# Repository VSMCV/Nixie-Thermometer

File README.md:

# Nixie-Thermometer
Hardware design and software files for a Nixie display thermometer

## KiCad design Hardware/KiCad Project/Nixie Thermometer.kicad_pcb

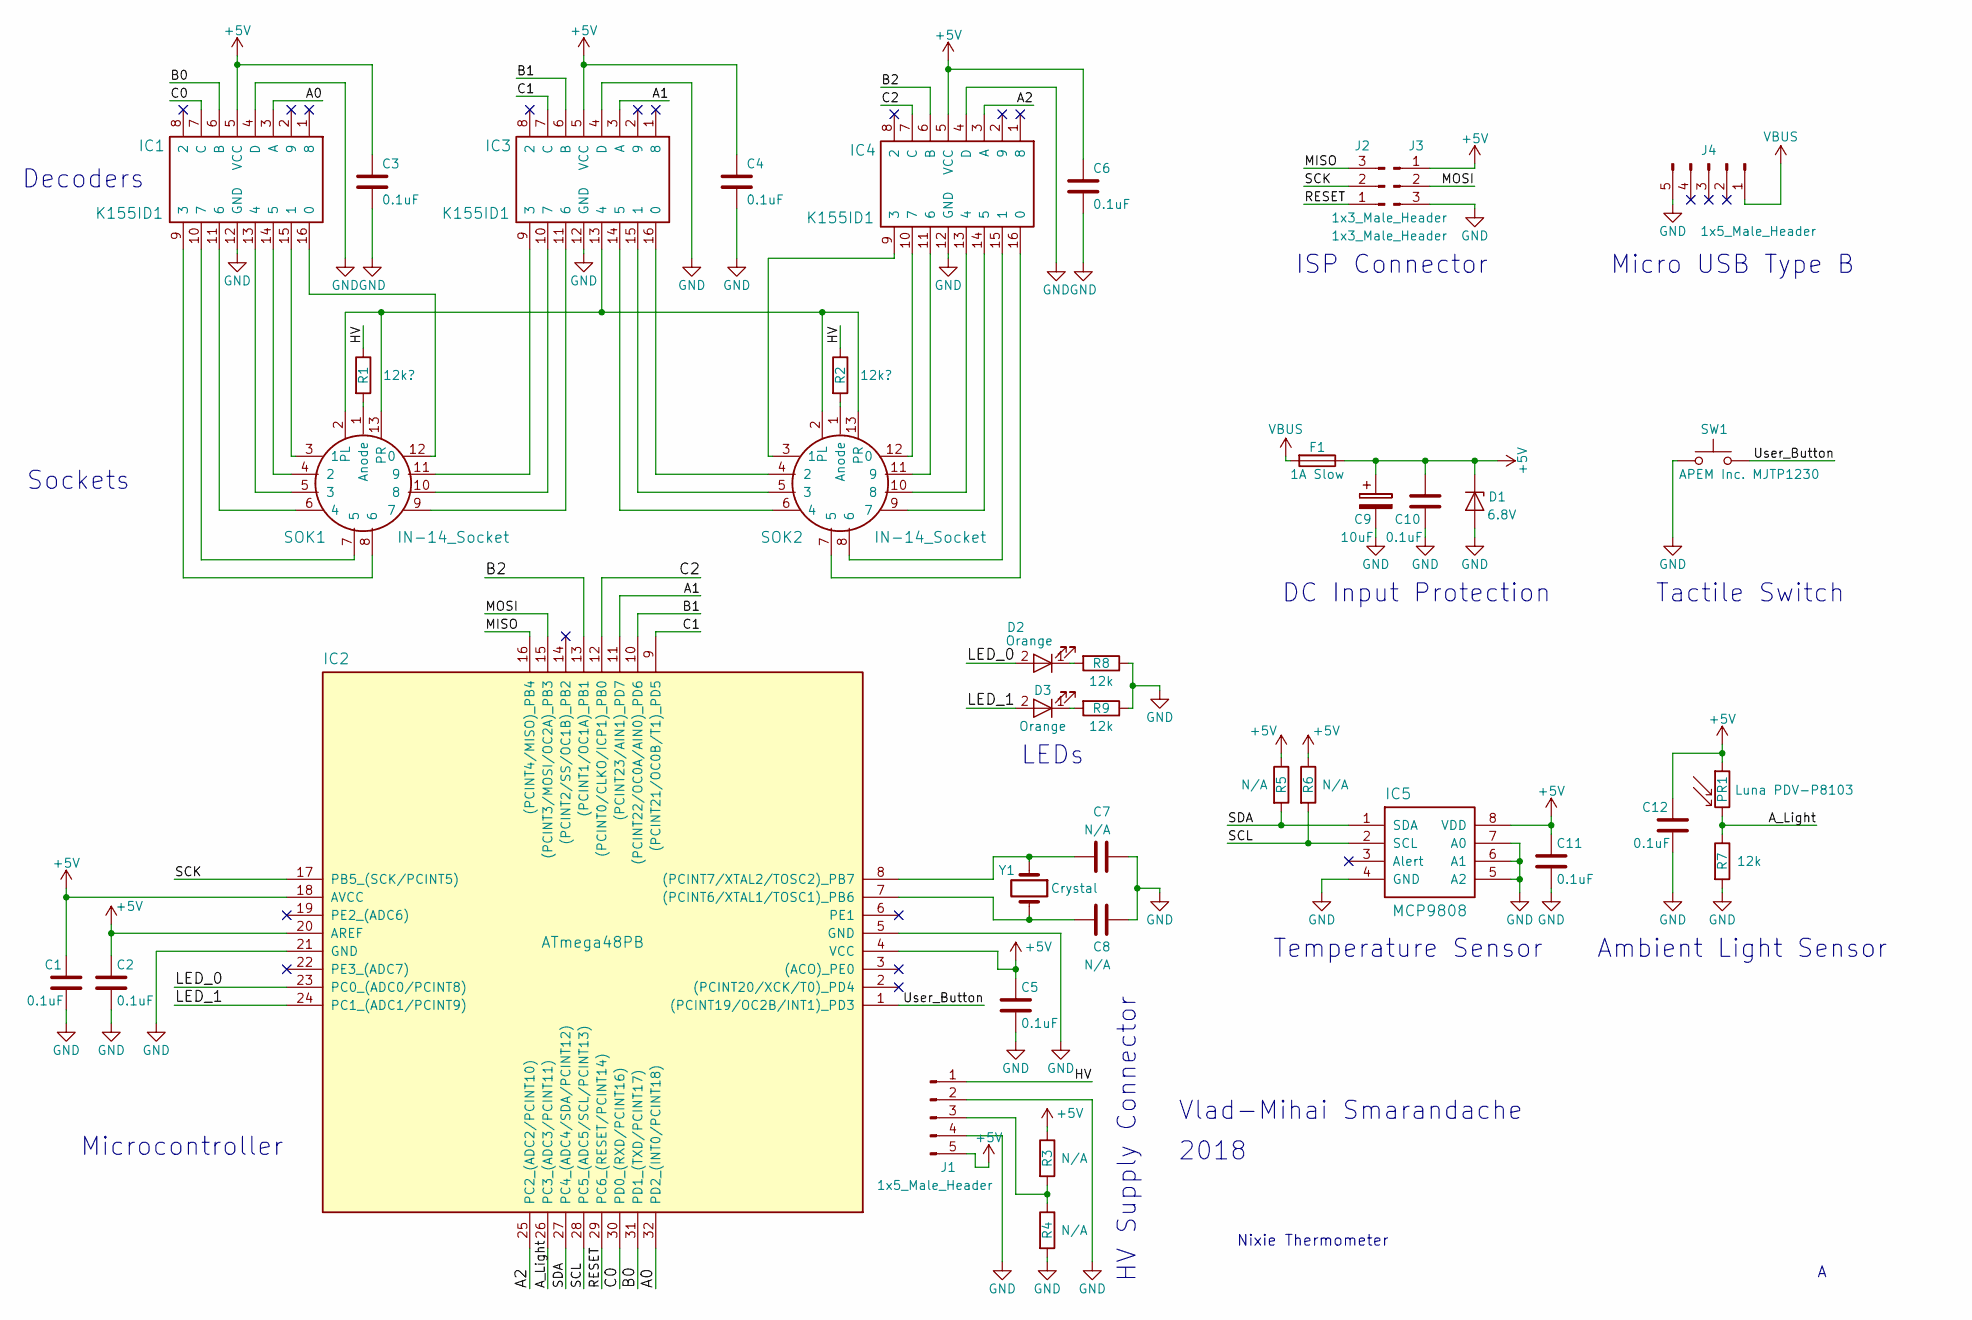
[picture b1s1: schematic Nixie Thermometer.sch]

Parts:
C1, C2, C3, C4, C5, C6, C10, C11, C12: 0.1uF; 0805_Capacitor_Handjob
C7, C8: N/A; 0805_Capacitor_Handjob
C9: 10uF; Polarized_Capacitor_4mm
D1: 6.8V; SOD-323_Diode
D2, D3: Orange; 0805_LED_Handjob
F1: 1A Slow; 1206_Fuse_Handjob
IC1, IC3, IC4: K155ID1; Soviet_DIPsky-16
IC2: ATmega48PB; TQFP-32_0.8mm_Pitch
IC5: MCP9808; MSOP-8_0.65mm_Pitch
J1: 1x5_Male_Header; 1x5_Male_Header_SMD_1-Left
J2, J3: 1x3_Male_Header
J4: 1x5_Male_Header
PR1: Luna PDV-P8103; Photoresistor_5.1x4.3mm
R1, R2: 12k?; 0805_Resistor_Handjob
R3, R4, R5, R6: N/A; 0805_Resistor_Handjob
R7, R8, R9: 12k; 0805_Resistor_Handjob
SOK1, SOK2: IN-14_Socket
SW1: APEM Inc. MJTP1230; Tactile_Switch_4mm
Y1: Crystal

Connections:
+5V: C1.1, C2.1, C3.1, C4.1, C5.1, C6.1, C9.1, C10.1, C11.1, C12.1, D1.1 (K), F1.1, IC1.5 (VCC), IC2.4 (VCC), IC2.18 (AVCC), IC2.20 (AREF), IC3.5 (VCC), IC4.5 (VCC), IC5.8 (VDD), J1.5, J3.1, PR1.1, R3.1, R5.1, R6.1
/A0: IC1.3 (A), IC2.32 (PD2_(INT0/PCINT18))
/A1: IC2.11 ((PCINT23/AIN1)_PD7), IC3.3 (A)
/A2: IC2.25 (PC2_(ADC2/PCINT10)), IC4.3 (A)
/A_Light: IC2.26 (PC3_(ADC3/PCINT11)), PR1.2, R7.1
/B0: IC1.6 (B), IC2.31 (PD1_(TXD/PCINT17))
/B1: IC2.10 ((PCINT22/OC0A/AIN0)_PD6), IC3.6 (B)
/B2: IC2.13 ((PCINT1/OC1A)_PB1), IC4.6 (B)
/C0: IC1.7 (C), IC2.30 (PD0_(RXD/PCINT16))
/C1: IC2.9 ((PCINT21/OC0B/T1)_PD5), IC3.7 (C)
/C2: IC2.12 ((PCINT0/CLKO/ICP1)_PB0), IC4.7 (C)
/HV: J1.1, R1.1, R2.1
/LED_0: D2.2 (A), IC2.23 (PC0_(ADC0/PCINT8))
/LED_1: D3.2 (A), IC2.24 (PC1_(ADC1/PCINT9))
/MISO: IC2.16 ((PCINT4/MISO)_PB4), J2.3
/MOSI: IC2.15 ((PCINT3/MOSI/OC2A)_PB3), J3.2
/RESET: IC2.29 (PC6_(RESET/PCINT14)), J2.1
/SCK: IC2.17 (PB5_(SCK/PCINT5)), J2.2
/SCL: IC2.28 (PC5_(ADC5/SCL/PCINT13)), IC5.2 (SCL), R6.2
/SDA: IC2.27 (PC4_(ADC4/SDA/PCINT12)), IC5.1 (SDA), R5.2
/User_Button: IC2.1 ((PCINT19/OC2B/INT1)_PD3), SW1.2
GND: C1.2, C2.2, C3.2, C4.2, C5.2, C6.2, C7.1, C8.1, C9.2, C10.2, C11.2, C12.2, D1.2 (A), IC1.4 (D), IC1.12 (GND), IC2.5 (GND), IC2.21 (GND), IC3.4 (D), IC3.12 (GND), IC4.4 (D), IC4.12 (GND), IC5.4 (GND), IC5.5 (A2), IC5.6 (A1), IC5.7 (A0), J1.2, J1.4, J3.3, J4.5, R4.2, R7.2, R8.1, R9.1, SW1.1
unnamed: C7.2, IC2.8 ((PCINT7/XTAL2/TOSC2)_PB7), Y1.1
unnamed: C8.2, IC2.7 ((PCINT6/XTAL1/TOSC1)_PB6), Y1.2
unnamed: D2.1 (K), R8.2
unnamed: D3.1 (K), R9.2
unnamed: IC1.9 (3), SOK1.8 (6)
unnamed: IC1.10 (7), SOK1.7 (5)
unnamed: IC1.11 (6), SOK1.6 (4)
unnamed: IC1.13 (4), SOK1.5 (3)
unnamed: IC1.14 (5), SOK1.4 (2)
unnamed: IC1.15 (1), SOK1.3 (1)
unnamed: IC1.16 (0), SOK1.12 (0)
unnamed: IC3.9 (3), SOK1.11 (9)
unnamed: IC3.10 (7), SOK1.10 (8)
unnamed: IC3.11 (6), SOK1.9 (7)
unnamed: IC3.13 (4), SOK1.2 (PL), SOK1.13 (PR), SOK2.2 (PL), SOK2.13 (PR)
unnamed: IC3.14 (5), SOK2.6 (4)
unnamed: IC3.15 (1), SOK2.5 (3)
unnamed: IC3.16 (0), SOK2.4 (2)
unnamed: IC4.9 (3), SOK2.3 (1)
unnamed: IC4.10 (7), SOK2.12 (0)
unnamed: IC4.11 (6), SOK2.11 (9)
unnamed: IC4.13 (4), SOK2.10 (8)
unnamed: IC4.14 (5), SOK2.9 (7)
unnamed: IC4.15 (1), SOK2.8 (6)
unnamed: IC4.16 (0), SOK2.7 (5)
unnamed: J1.3, R3.2, R4.1
unnamed: R1.2, SOK1.1 (Anode)
unnamed: R2.2, SOK2.1 (Anode)
VBUS: F1.2, J4.1

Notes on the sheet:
Nixie Thermometer
Vlad-Mihai Smarandache
2018
Decoders
Sockets
ISP Connector
Micro USB Type B
DC Input Protection
Tactile Switch
Temperature Sensor
Ambient Light Sensor
Microcontroller
HV Supply Connector
LEDs

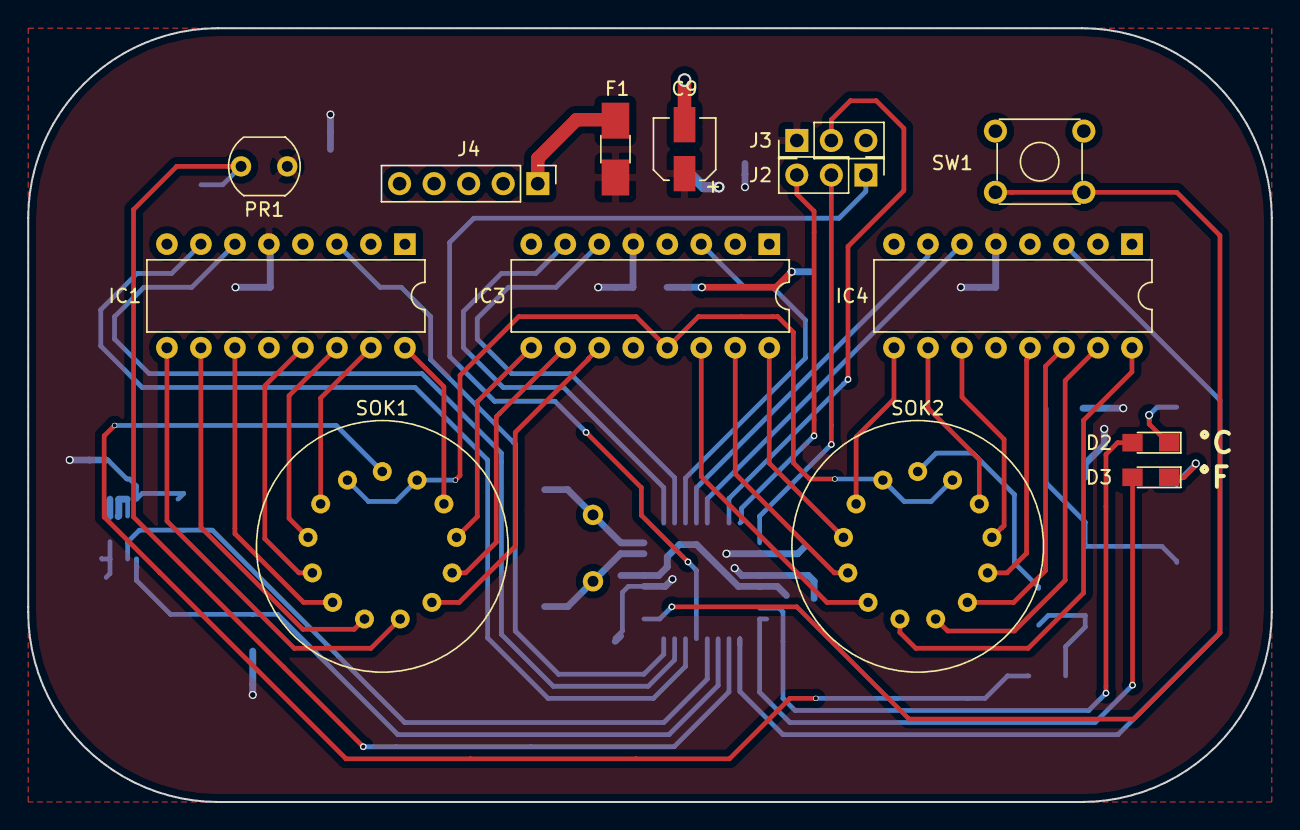
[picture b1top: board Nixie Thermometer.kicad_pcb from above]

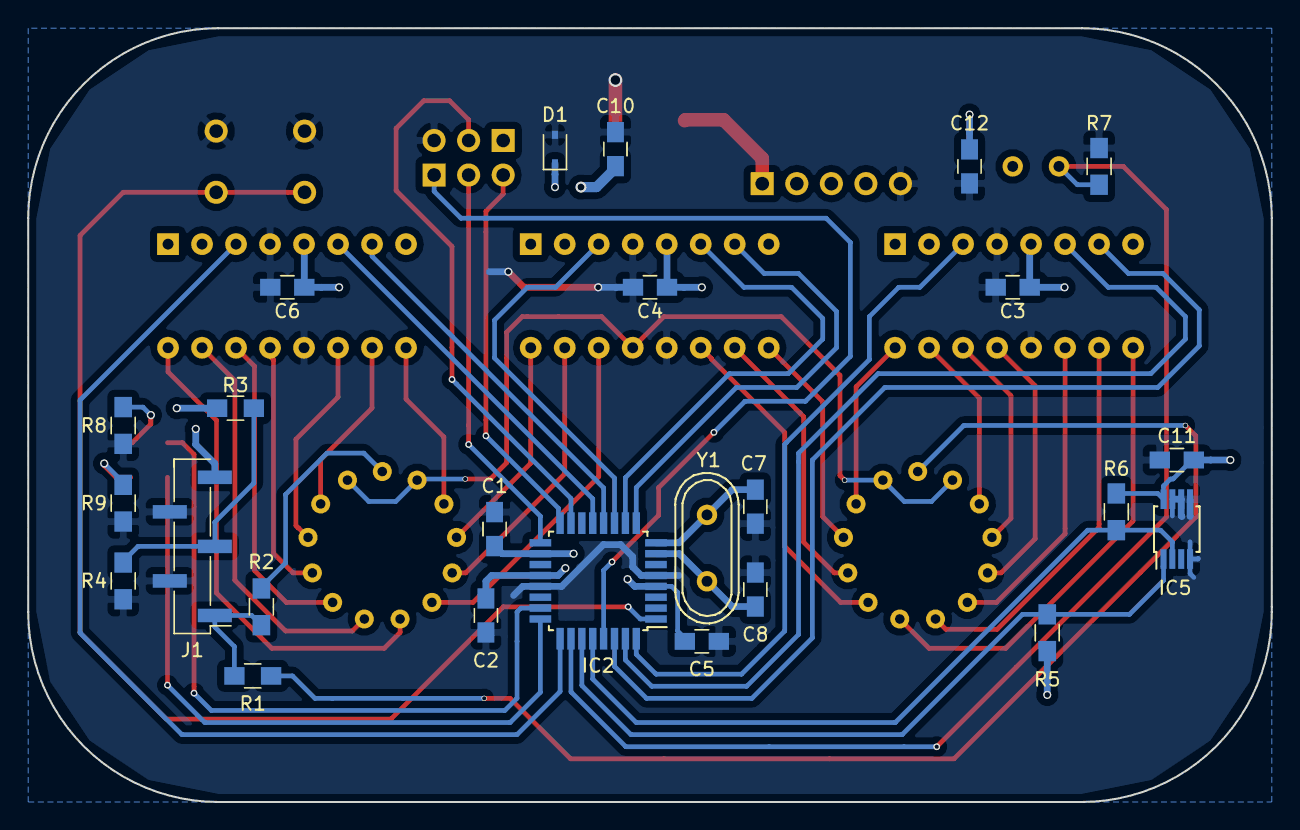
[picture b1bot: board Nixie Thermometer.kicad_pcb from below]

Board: 2 copper layers, 91.4 x 56.9 mm, 39 parts (25 on the bottom side), 51 nets.
